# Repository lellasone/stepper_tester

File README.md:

# stepper_tester
This was a quick one-off stepper tester board. This version uses a TMC2208 from Trinamic. 

The idea for this version was to test out if the TMC2208 is really a drop in
replacement for it's competetors in practice (spoiler: it is!). A few (very)
minor improvements have been made to the code, but it actually ran with only
new pin mappings and no other changes the first time I uploaded it.

## Making Changes
For pcb design files look in PCB (KiCAD). For the arduino code look in the 
stepper_driver directory. 

You can upload code to the board using your ISP programmer of choice (I use 
tinyISP) with the fuse settings and pin mappings for a pro-mini.  

## Operating Instructions
* Move the joystick up and down to change the pulse frequency within a single micro-stepping band (zero centered).
* Flick the joystick side to side to change the microstepping level. (faster to the left)
    * To read the current microstepping level, count the status LED's pulses.
* To disable output, connect the jumper by the joystick.

## Firmware Depends
The sketch uses a few Arduino libraries (below) all of which can be 
installed from within the Arduino IDE using the standard library tool.
* PWM Freak - convenience functions for setting pwm devisor values. 
* TIMER1 - convenience functions for timer interrupts

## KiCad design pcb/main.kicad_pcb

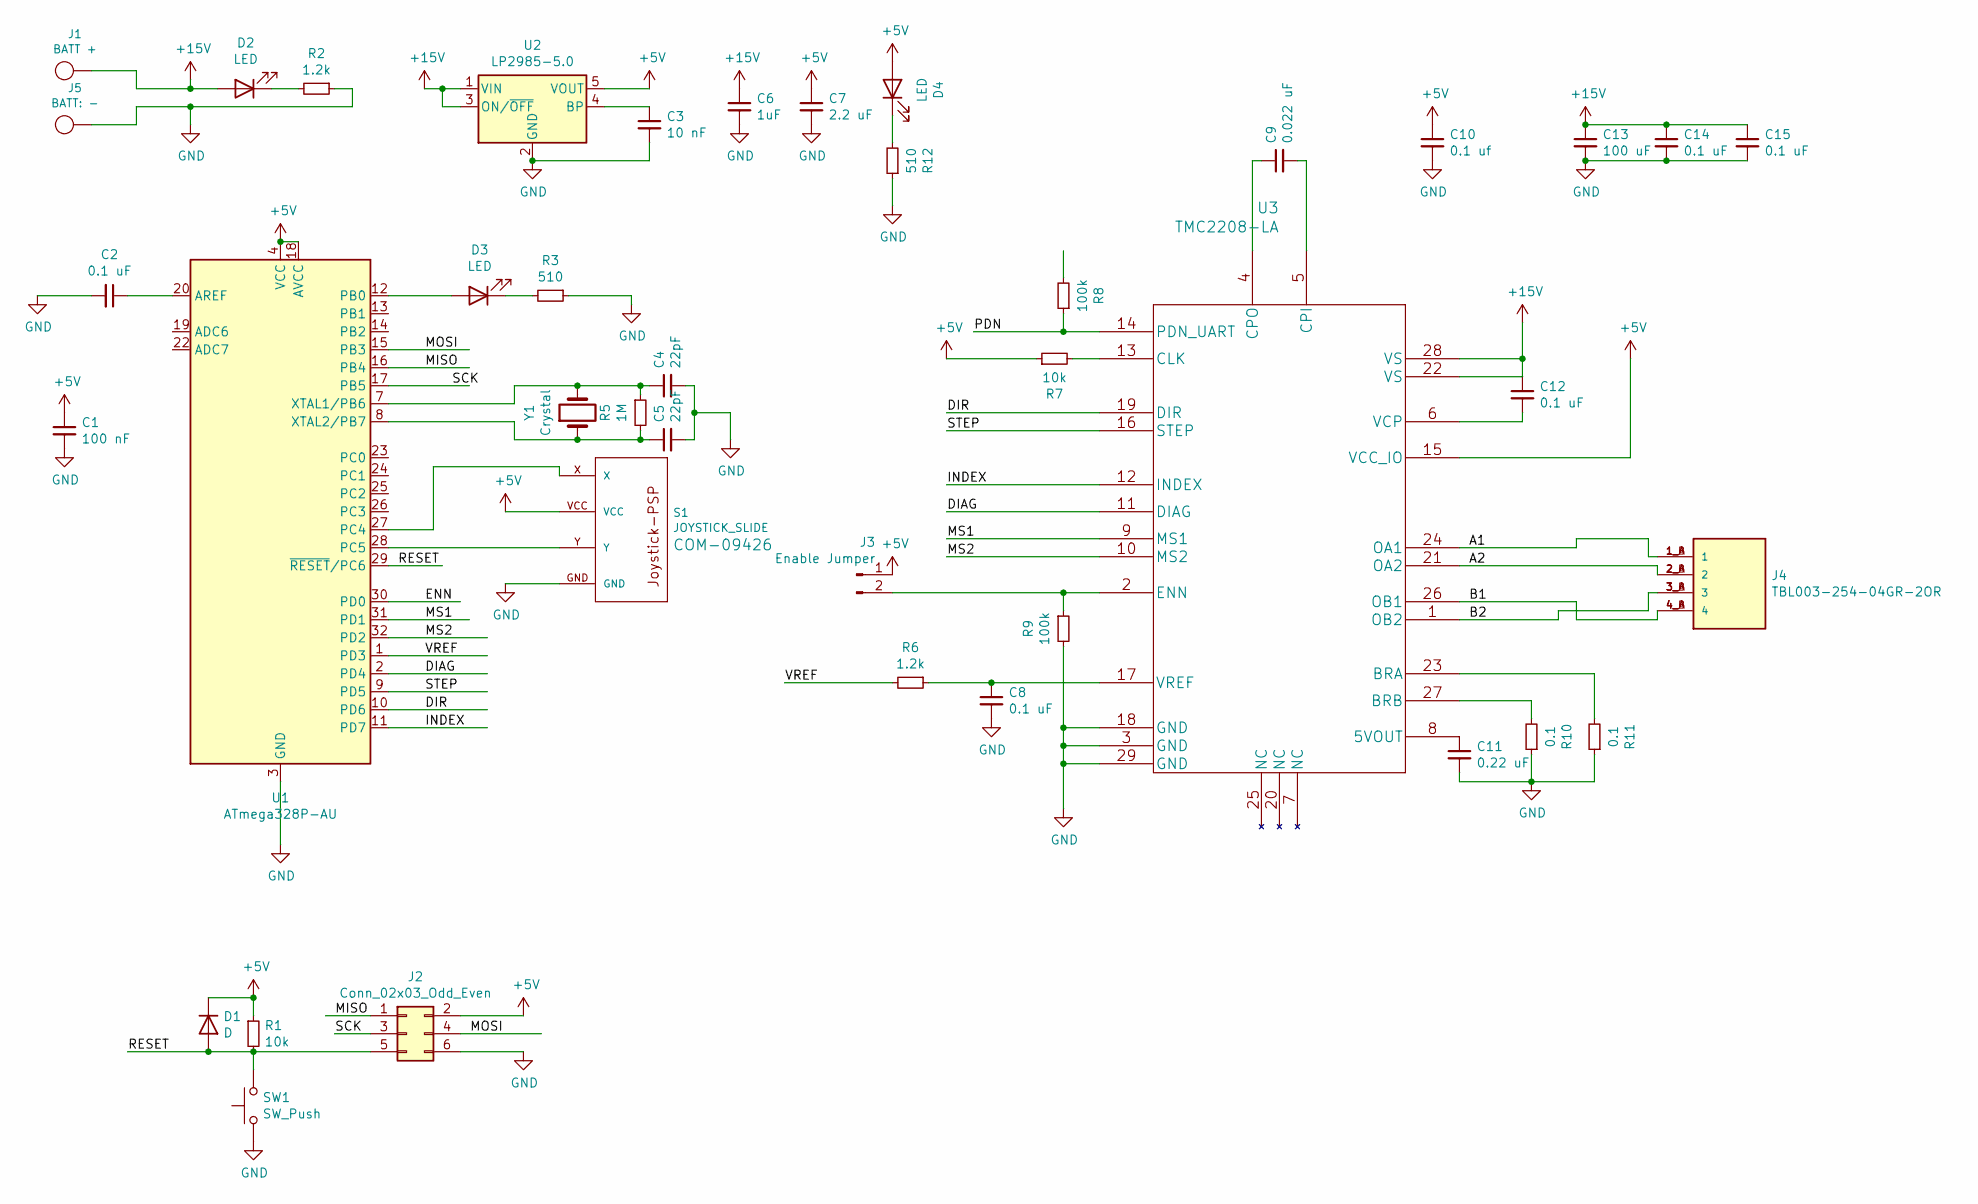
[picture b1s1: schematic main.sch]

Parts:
C1: 100 nF; C_0603_1608Metric; LCSC C14663
C2, C8, C12, C14, C15: 0.1 uF; C_0603_1608Metric; LCSC C14663
C3: 10 nF; C_0603_1608Metric; LCSC C57112
C4, C5: 22pF; C_0603_1608Metric; LCSC C1653
C6: 1uF; C_0603_1608Metric; LCSC C15849
C7: 2.2 uF; C_0805_2012Metric; LCSC C49217
C9: 0.022 uF; C_0402_1005Metric; LCSC C1532
C10: 0.1 uf; C_0603_1608Metric; LCSC C14663
C11: 0.22 uF; C_0603_1608Metric; LCSC C21120
C13: 100 uF; CP_Elec_8x10
D1: D; D_2010_5025Metric; LCSC C412437
D2: LED; D_0603_1608Metric; LCSC C84256
D3: LED; D_0805_2012Metric; LCSC C2293
D4: LED; D_0805_2012Metric; LCSC C63855
J1: BATT +; BANANA_CONN
J2: Conn_02x03_Odd_Even; PinHeader_2x03_P2.54mm_Vertical
J3: Enable Jumper; PinHeader_1x02_P2.54mm_Horizontal
J4: TBL003-254-04GR-2OR; header
J5: BATT: -; BANANA_CONN
R1, R7: 10k; R_0603_1608Metric; LCSC C22859
R2, R6: 1.2k; R_0603_1608Metric; LCSC C22765
R3, R12: 510; R_0603_1608Metric; LCSC C23193
R5: 1M; R_0603_1608Metric; LCSC C22935
R8, R9: 100k; R_0603_1608Metric; LCSC C25803
R10, R11: 0.1; R_1206_3216Metric; LCSC C25334
S1: JOYSTICK_SLIDE; JOYSTICK-PSP1000
SW1: SW_Push; SW_SPST_TL3342
U1: ATmega328P-AU; TQFP-32_7x7mm_P0.8mm; LCSC C14877
U2: LP2985-5.0; SOT-23-5
U3: TMC2208-LA; LCSC C115944
Y1: Crystal; Crystal_SMD_5032-2Pin_5.0x3.2mm_HandSoldering; LCSC C115962

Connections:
+5V: C1.1, C7.1, C10.1, D1.1 (K), D4.2 (A), J2.2, J3.1, R1.1, R7.1, S1.VCC, U1.4 (VCC), U1.6 (VCC), U1.18 (AVCC), U2.5 (VOUT), U3.15 (VCC_IO)
+15V: C6.1, C12.1, C13.1, C14.1, C15.1, D2.2 (A), J1.1, U2.1 (VIN), U2.3 (ON/~OFF~), U3.22 (VS), U3.28 (VS)
/A1: J4.1_A (1), J4.1_B (1), U3.24 (OA1)
/A2: J4.2_A (2), J4.2_B (2), U3.21 (OA2)
/B1: J4.4_A (4), J4.4_B (4), U3.26 (OB1)
/B2: J4.3_A (3), J4.3_B (3), U3.1 (OB2)
/DIAG: U1.2 (PD4), U3.11 (DIAG)
/DIR: U1.10 (PD6), U3.19 (DIR)
/ENN: U1.30 (PD0)
/INDEX: U1.11 (PD7), U3.12 (INDEX)
/MISO: J2.1, U1.16 (PB4)
/MOSI: J2.4, U1.15 (PB3)
/MS1: U1.31 (PD1), U3.9 (MS1)
/MS2: U1.32 (PD2), U3.10 (MS2)
/PDN: R8.1, U3.14 (PDN_UART)
/RESET: D1.2 (A), J2.5, R1.2, SW1.2, U1.29 (~RESET~/PC6)
/SCK: J2.3, U1.17 (PB5)
/STEP: U1.9 (PD5), U3.16 (STEP)
/VREF: R6.2, U1.1 (PD3)
GND: C1.2, C2.2, C3.2, C4.2, C5.2, C6.2, C7.2, C8.2, C10.2, C11.2, C13.2, C14.2, C15.2, J2.6, J5.1, R2.1, R3.1, R9.2, R10.1, R11.1, R12.1, S1.GND, SW1.1, U1.3 (GND), U1.5 (GND), U1.21 (GND), U2.2 (GND), U3.3 (GND), U3.18 (GND), U3.29 (GND)
unnamed: C2.1, U1.20 (AREF)
unnamed: C3.1, U2.4 (BP)
unnamed: C4.1, R5.1, U1.7 (XTAL1/PB6), Y1.2
unnamed: C5.1, R5.2, U1.8 (XTAL2/PB7), Y1.1
unnamed: C8.1, R6.1, U3.17 (VREF)
unnamed: C9.1, U3.4 (CPO)
unnamed: C9.2, U3.5 (CPI)
unnamed: C11.1, U3.8 (5VOUT)
unnamed: C12.2, U3.6 (VCP)
unnamed: D2.1 (K), R2.2
unnamed: D3.1 (K), R3.2
unnamed: D3.2 (A), U1.12 (PB0)
unnamed: D4.1 (K), R12.2
unnamed: J3.2, R9.1, U3.2 (ENN)
unnamed: R7.2, U3.13 (CLK)
unnamed: R10.2, U3.27 (BRB)
unnamed: R11.2, U3.23 (BRA)
unnamed: S1.X, U1.27 (PC4)
unnamed: S1.Y, U1.28 (PC5)

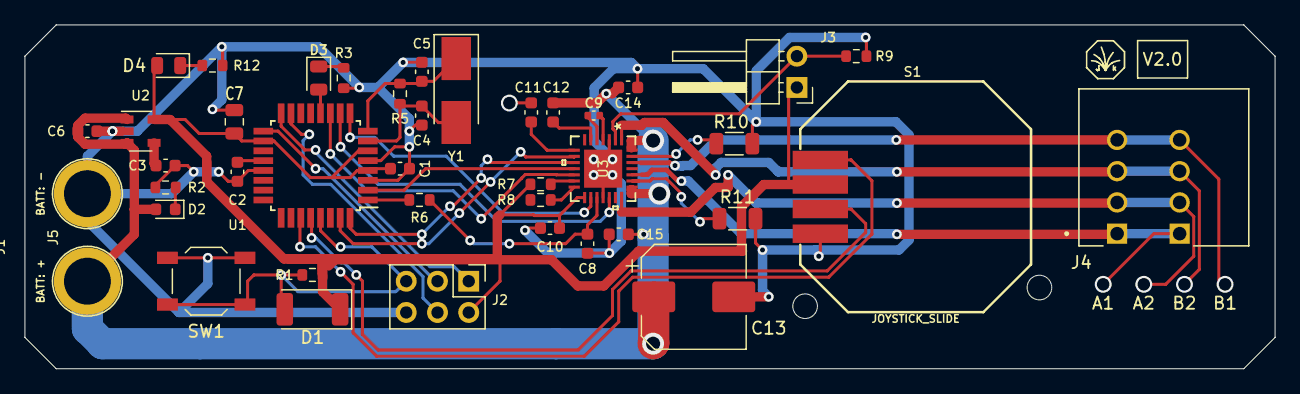
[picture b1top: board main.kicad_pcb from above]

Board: 2 copper layers, 101.6 x 27.9 mm, 41 parts (0 on the bottom side), 38 nets.

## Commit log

2019-08-18 :space_invader: Added .gitattributes & .gitignore files
2019-08-18 initial commit
    adds pcb files, firmware files, and various pieces of documentation
2019-08-19 added skeleton of set pps
2019-08-23 Now working
    Major changes to firmware, minor reworks on pcb.
2021-03-04 Added a readme
    You still shouldn't use this version (V2 is immeasurably better), but now it is prettier .
2021-03-04 added files for trnamic test board 2208
2021-03-04 deleted a bunch of stuff
2021-03-04 deleted the last of the DR8825 items
2021-03-04 added support for the mode readout LED
2021-03-04 added photo
2021-03-04 fixed magic number in current set function
2021-03-27 interrupt based stepping enabled, full speed range enabled, still pins to rails too early, and acceleration curves not adequate, current limit insufficient to prevent overheating
2021-03-30 compress period setting, does not work
2021-03-30 acceleration working but not tuned, all modes can reach full speed at 5khz max, but some order of reduction may be reversed
2021-03-30 everything is broken
2021-03-31 velocity curve now linear
2021-04-07 nothing works
2021-04-12 final changes to v2.0

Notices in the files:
parts and their libraries:
Copyright 2016 Accelerated Designs. All rights reserved.
